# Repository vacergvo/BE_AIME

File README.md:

# Smart Device Project: Nanoparticle Gas Sensor & IoT Shield
**UF "Smart Devices" – PTP Innovative Smart System (ISS)**

## 1. Project Overview
This project is part of the **5ISS program at INSA Toulouse**. It focuses on the development of a **nanoparticle-based gas sensing system**, designed and characterized at **AIME**, the INSA Toulouse laboratory.

The project covers the full development cycle, from sensor fabrication to data visualization. A custom **PCB** was designed, and **ESP32 firmware** was developed to exploit the gas sensor measurements and transmit the data wirelessly. The collected data is then processed and displayed on a **web-based interface**.

The system relies on **LoRa communication** for long-range data transmission and integrates both hardware and software components.

The development chain consists of :

- Hardware design (analog signal amplified through a 2-stage transimpedance amplifier tested with LTSpice and PCB design with Kicad),

- Embedded software development using Arduino,

- LoRa wireless communication,

- Data processing and visualization using Node-RED,

- Mobile application development using MIT App Inventor.

## 2. The Measurement Chain
### Nanoparticle Gas Sensor (AIME)
Developed during a training period at AIME, this sensor utilizes:
* **Synthesis**: Nanoparticles produced and deposited by dielectrophoresis.
* **Active Zone**: A sensitive layer of $WO_3$ nanoparticles integrated on aluminum interdigitated combs.
* **Target Gases**: High sensitivity to Ethanol and Ammonium.
* **Control**: Features an internal poly-silicon heating resistor and an aluminum temperature sensor.

### Analog Interface Circuit
The sensor is interfaced via a transimpedance circuit designed to measure its resistance.
* **Amplification**: Utilizes an LTC1050 precision chopper amplifier.
* **Filtering**: A low-pass filter is implemented to extract useful signals before the ADC stage.
* **Simulation**: The circuit was validated using LTSpice IV.

---

## 3. Hardware Design (KiCad)
The PCB shield was designed following specific technical constraints to ensure compatibility with an Arduino UNO.

### Design Constraints:
* **Track Width**: 0.5 mm minimum.
* **Track Isolation**: 0.5 mm minimum.
* **Drill Sizes**: 1mm for headers/connectors; 0.8mm for passive components.

### Schematic & Routing

### 3D Model

---

## 4. Implementation & Software
* **Microcontroller**: Programmed for Arduino UNO / ESP32 platforms.
* **Connectivity**: Configured to send data over the The Things Network (TTN) via LoRa.
* **Version Control**: Developed collaboratively using Git and GitHub.
* **Interface**: NodeRed Application.

## 5. Repository Structure
* `/PCB_Capteur`: Schematic and Layout design files.
* `/Software`: Arduino/ESP32 source code for data acquisition.
* `/Spice`: Simulation files for the analog interface.
* `/Images`: Screenshots and documentation assets.

## 6. Authors & Credits
* **Student**: Tom Lassalle, Sandra Benjaoui, Louis Rousset
* **Supervisors**: J. Grisolia, A. Biganzoli, C. Crouzet, B. Mestre.
* **Partners**: AIME Toulouse (Atelier Interuniversitaire de Micro-nano Électronique).

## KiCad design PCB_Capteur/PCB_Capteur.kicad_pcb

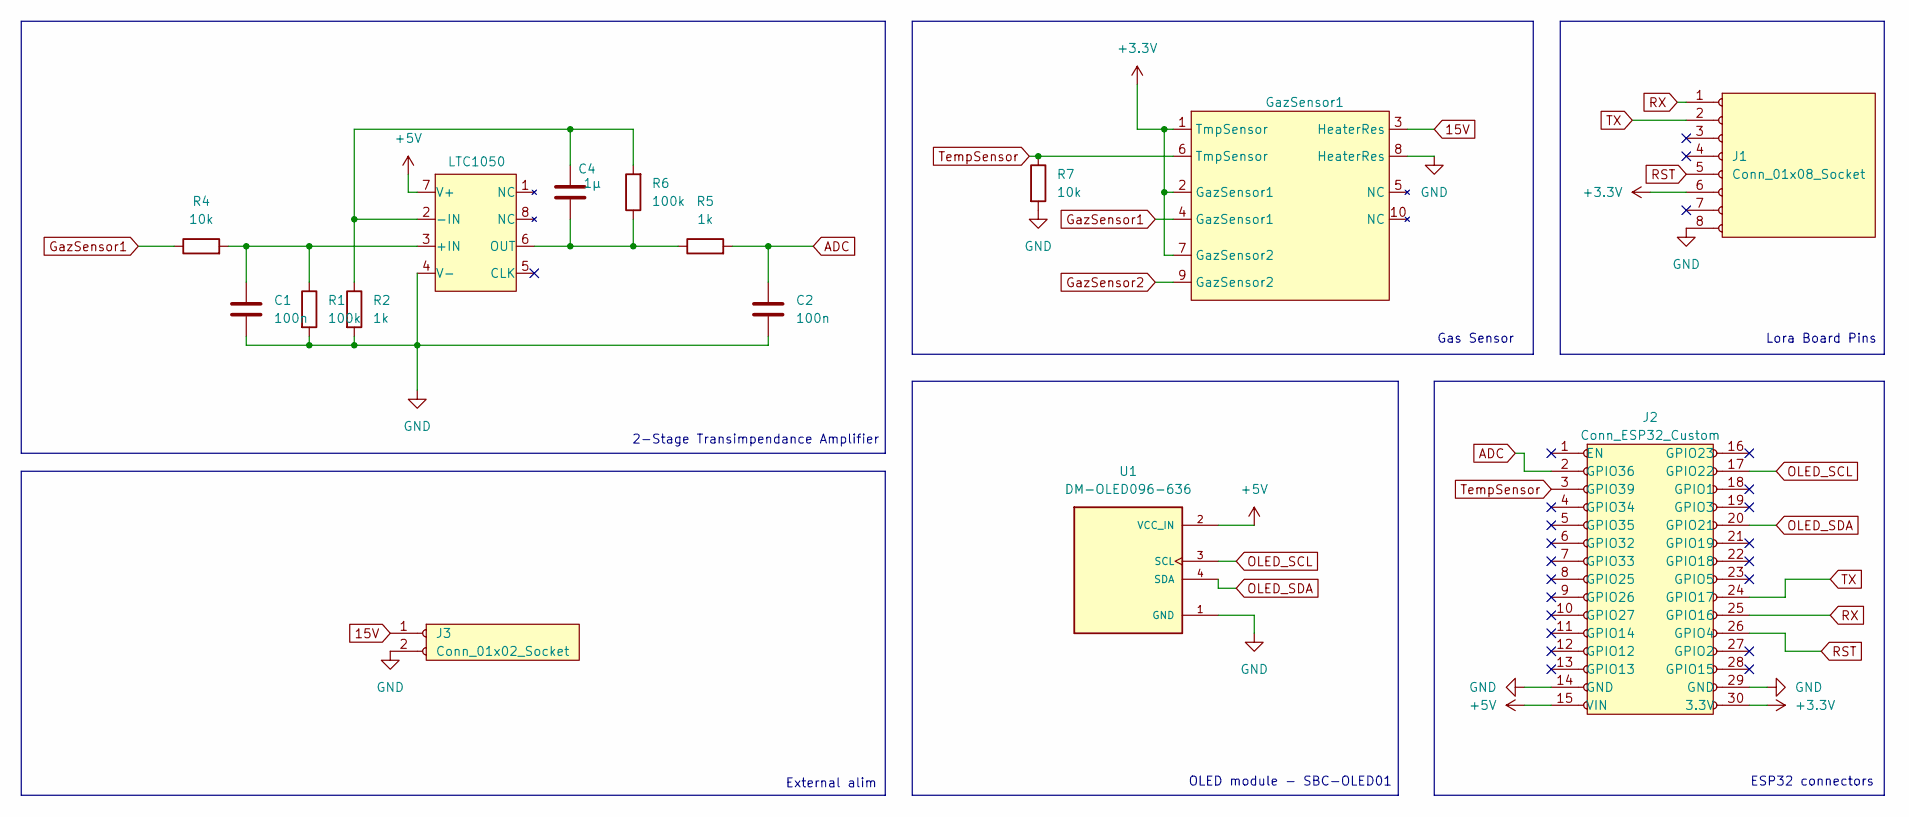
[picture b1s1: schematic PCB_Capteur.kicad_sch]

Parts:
C1, C2: 100n; C_Disc_D5.1mm_W3.2mm_P5.00mm
C4: 1µ; C_Rect_L7.5mm_W6.5mm_P5.00mm
GazSensor1: TO-5-10_Window
J1: Conn_01x08_Socket; PinSocket_1x08_P2.54mm_Vertical
J2: Conn_ESP32_Custom; Custom
J3: Conn_01x02_Socket; PinSocket_1x02_P2.54mm_Vertical
LTC1050: SO-8_S
R1, R6: 100k; R_Axial_DIN0207_L6.3mm_D2.5mm_P10.16mm_Horizontal
R2, R5: 1k; R_Axial_DIN0207_L6.3mm_D2.5mm_P10.16mm_Horizontal
R4, R7: 10k; R_Axial_DIN0207_L6.3mm_D2.5mm_P10.16mm_Horizontal
U1: DM-OLED096-636; MODULE_DM-OLED096-636; PARTREV 2018-09-10

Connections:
15V: GazSensor1.3 (HeaterRes), J3.1; also elsewhere on the board
+3.3V: GazSensor1.1 (TmpSensor), GazSensor1.2 (GazSensor1), GazSensor1.7 (GazSensor2), J1.6, J2.30 (3.3V); also elsewhere on the board
+5V: J2.15 (VIN), LTC1050.7 (V+), U1.2 (VCC_IN)
ADC: C2.1, J2.2 (GPIO36), R5.2
GND: C1.2, C2.2, GazSensor1.8 (HeaterRes), J1.8, J2.14 (GND), J2.29 (GND), J3.2, LTC1050.4 (V-), R1.2, R2.2, R7.2, U1.1 (GND); also elsewhere on the board
GazSensor1: GazSensor1.4 (GazSensor1), R4.1; also elsewhere on the board
unnamed: C1.1, LTC1050.3 (+IN), R1.1, R4.2
unnamed: C4.1, LTC1050.2 (-IN), R2.1, R6.2
unnamed: C4.2, LTC1050.6 (OUT), R5.1, R6.1
OLED_SCL: J2.17 (GPIO22), U1.3 (SCL)
OLED_SDA: J2.20 (GPIO21), U1.4 (SDA)
RST: J1.5, J2.26 (GPIO4)
RX: J1.1, J2.25 (GPIO16)
TX: J1.2, J2.24 (GPIO17)
TempSensor: GazSensor1.6 (TmpSensor), J2.3 (GPIO39), R7.1; also elsewhere on the board

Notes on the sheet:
External alim
OLED module - SBC-OLED01
Gas Sensor
2-Stage Transimpendance Amplifier
Lora Board Pins
ESP32 connectors

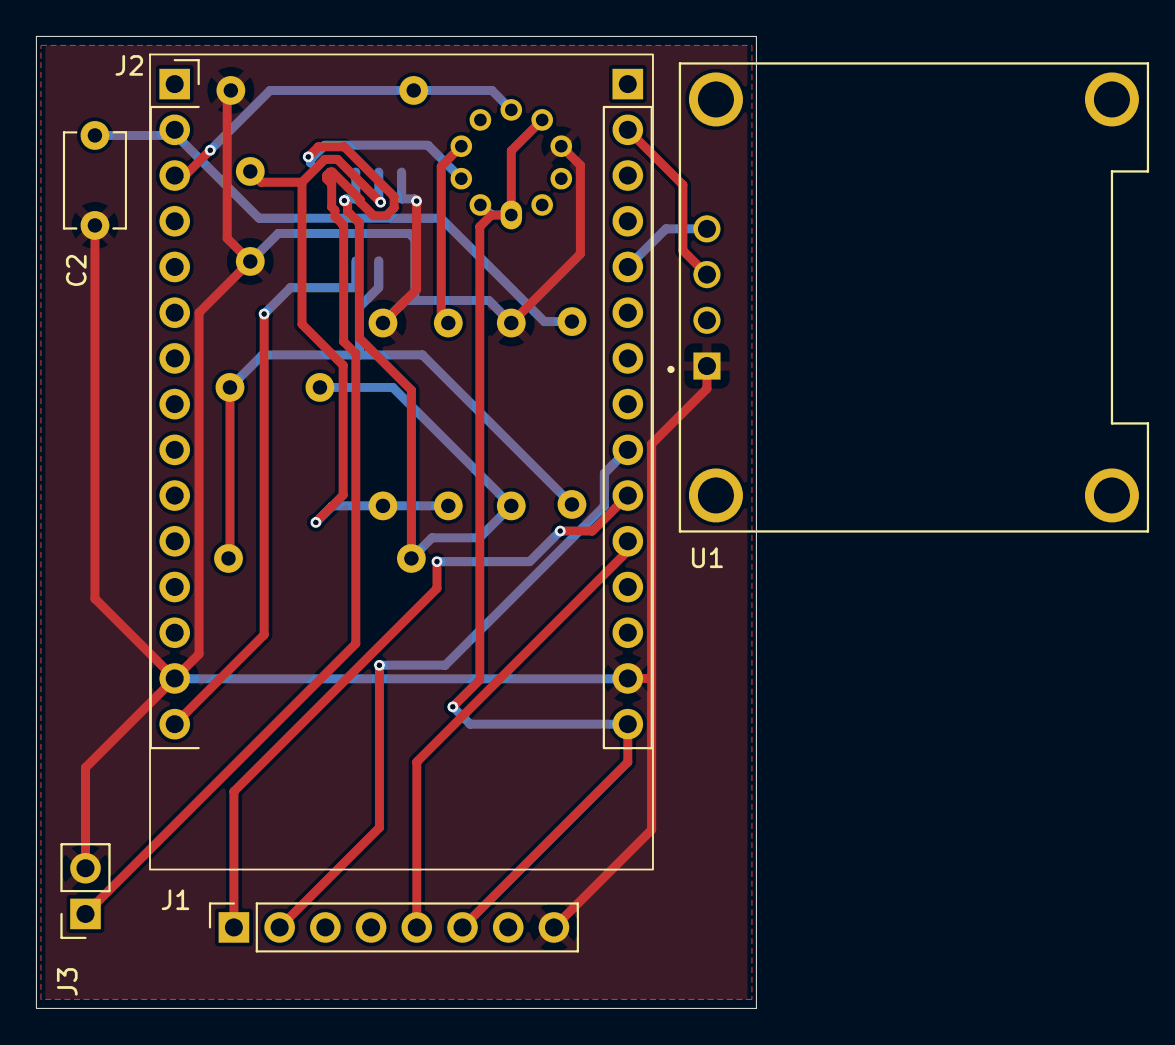
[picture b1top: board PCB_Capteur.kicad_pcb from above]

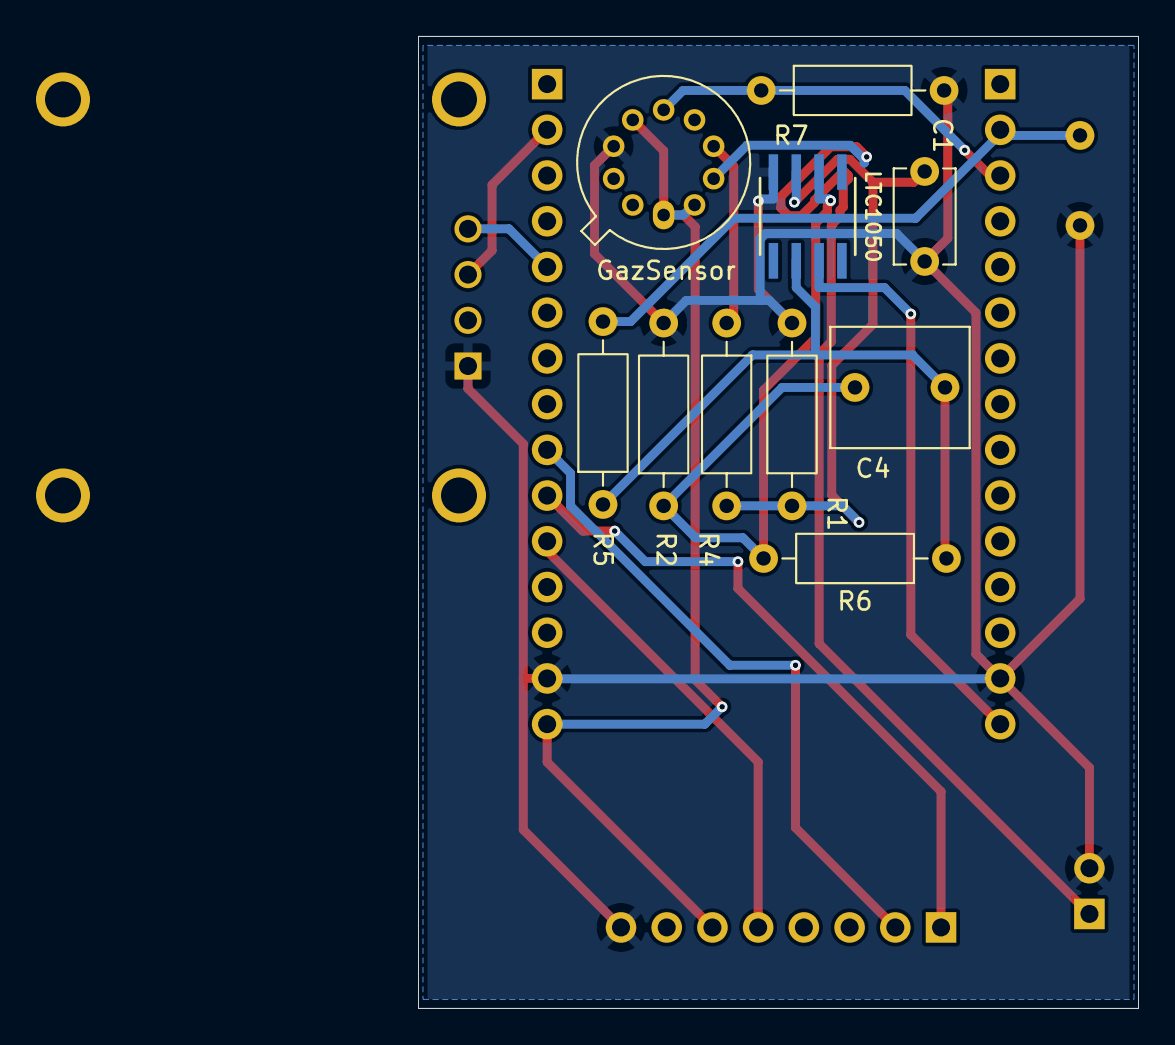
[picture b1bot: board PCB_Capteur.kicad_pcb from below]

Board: 2 copper layers, 40.0 x 54.0 mm, 15 parts (10 on the bottom side), 15 nets.

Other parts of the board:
GazSensor: TO-5-10_Window

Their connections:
15V: GazSensor.3 (HeaterRes); also elsewhere on the board
+3.3V: GazSensor.1 (TmpSensor), GazSensor.2 (GazSensor1), GazSensor.7 (GazSensor2); also elsewhere on the board
GND: GazSensor.8 (HeaterRes); also elsewhere on the board
GazSensor1: GazSensor.4 (GazSensor1); also elsewhere on the board
TempSensor: GazSensor.6 (TmpSensor); also elsewhere on the board

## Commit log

2025-12-08 Kicad amplification stage
2025-12-17 [ADD] soft LoRa
2026-01-06 PCB Update + Amplification stage simulation
2026-01-06 PCB Improvements
2026-01-06 PCB Optimizations
2026-01-09 Revise README with project details and structure
2026-01-09 Adding Images for the readme
2026-01-09 Revise README with images
2026-01-09 Update README
    Removed placeholder text for screenshots and updated 3D model image references.
2026-01-09 Update README
    Removed unnecessary citation references and cleaned up the text formatting in the project overview section.
2026-01-09 Adding LTSpice screenshot
2026-01-09 Change LTSpice simulation image to PNG format
2026-01-09 Update intro readme
2026-01-09 Modif intro
2026-01-09 New soft
